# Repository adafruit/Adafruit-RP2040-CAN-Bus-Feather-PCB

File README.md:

## Adafruit RP2040 CAN Bus Feather with MCP2515 CAN Controller - STEMMA QT PCB

<a href="http://www.adafruit.com/products/5724"><br/>
Click here to purchase one from the Adafruit shop</a>

PCB files for the Adafruit RP2040 CAN Bus Feather with MCP2515 CAN Controller - STEMMA QT. 

Format is EagleCAD schematic and board layout
* https://www.adafruit.com/product/5724

### Description

If you'd like to quickly get started with CAN bus interfacing, with no soldering required, our Adafruit RP2040 CAN Bus Feather comes ready-to-rock with a microcontroller, CAN chipset and terminal blocks for instant gratification. The controller used is the MCP26525 (aka a MCP2515 with built-in transciever), an extremely popular and well-supported chipset that has drivers in Arduino and CircuitPython and only requires an SPI port and two pins for chip-select and IRQ. Use it to send and receive messages in either standard or extended format at up to 1 Mbps.

Feather is the development board specification from Adafruit, and like its namesake, it is thin, light, and lets you fly! We designed Feather to be a new standard for portable microcontroller cores. We have other boards in the Feather family, check'em out here.

CAN Bus is a small-scale networking standard, originally designed for cars and, yes, busses, but is now used for many robotics or sensor networks that need better range and addressing than I2C and don't have the pins or computational ability to talk on Ethernet. CAN is 2 wire differential, which means it's good for long distances and noisy environments.

Messages are sent at about 1Mbps rate - you set the frequency for the bus and then all 'joiners' must match it, and have an address before the packet so that each node can listen in to messages just for it. New nodes can be attached easily because they just need to connect to the two data lines anywhere in the shared net. Each CAN device sends messages whenever it wants, and thanks to some clever data encoding, can detect if there's a message collision and retransmit later. 

We've added a few nice extras to this Feather to make it useful in many common CAN scenarios:

* 5V charge-pump voltage generator, so even though you are running 3.3V on a Feather board, it will generate a nice clean 5V as required by the interal transceiver.
* 3.5mm soldered terminal block quick access to the High and Low data lines as well as a ground pin, without any soldering.
* 120-ohm termination resistor on board, you can remove the termination easily by cutting the jumper marked TERM on the top of the board.
* CAN control CS, Reset, Int, standby pins connected internally so you can use any FeatherWing without pin conflicts.

At the Feather's heart is an RP2040 chip, clocked at 133 MHz and at 3.3V logic, the same one used in the Raspberry Pi Pico. This chip has a whopping 8 MB of onboard QSPI FLASH and 264K of RAM!  There's even room left over for a STEMMA QT connector for plug-and-play of I2C devices.

To make it easy to use for portable projects, we added a connector for any of our 3.7V Lithium polymer batteries and built-in battery charging. You don't need a battery, it will run just fine straight from the USB Type C connector. But, if you do have a battery, you can take it on the go, then plug in the USB to recharge. The Feather will automatically switch over to USB power when it's available.

Here're some handy specs! You get:

* Measures 2.0" x 0.9" x 0.28" (50.8mm x 22.8mm x 7mm) without headers soldered in
* Light as a (large?) feather - 6.3 grams
* RP2040 32-bit Cortex M0+ dual core running at ~133 MHz @ 3.3V logic and power
* 264 KB RAM
* 8 MB SPI FLASH chip for storing files, images and CircuitPython/MicroPython code storage. No EEPROM
* Tons of GPIO! 21 x GPIO pins with following capabilities:
	* Four 12-bit ADCs (one more than Pico)
	* Two I2C, Two SPI, and two UART peripherals, we label one for the 'main' interface in standard Feather locations
	* 16 x PWM outputs - for servos, LEDs, etc
* Built-in 200mA+ lipoly charger with charging status indicator LED
* Pin #13 red LED for general purpose blinking
* RGB NeoPixel for full-color indication.
* On-board STEMMA QT connector that lets you quickly connect any Qwiic, STEMMA QT or Grove I2C devices with no soldering!
* Both Reset button and Bootloader select button for quick restarts (no unplugging-replugging to relaunch code)
* USB Type C connector lets you access built-in ROM USB bootloader and serial port debugging
* 3.3V regulator with 500mA peak current output and power enable pin
* 4 mounting holes
* 12 MHz crystal for perfect timing.
* Support circuitry for CAN Bus using SPI interface

Comes assembled and tested, with some header. You'll need a soldering iron to attach the header for installing onto your Feather. Stacking headers will let you put another FeatherWing on top.

### License

Adafruit invests time and resources providing this open source design, please support Adafruit and open-source hardware by purchasing products from [Adafruit](https://www.adafruit.com)!

Designed by Limor Fried/Ladyada for Adafruit Industries.

Creative Commons Attribution/Share-Alike, all text above must be included in any redistribution. 
See license.txt for additional details.

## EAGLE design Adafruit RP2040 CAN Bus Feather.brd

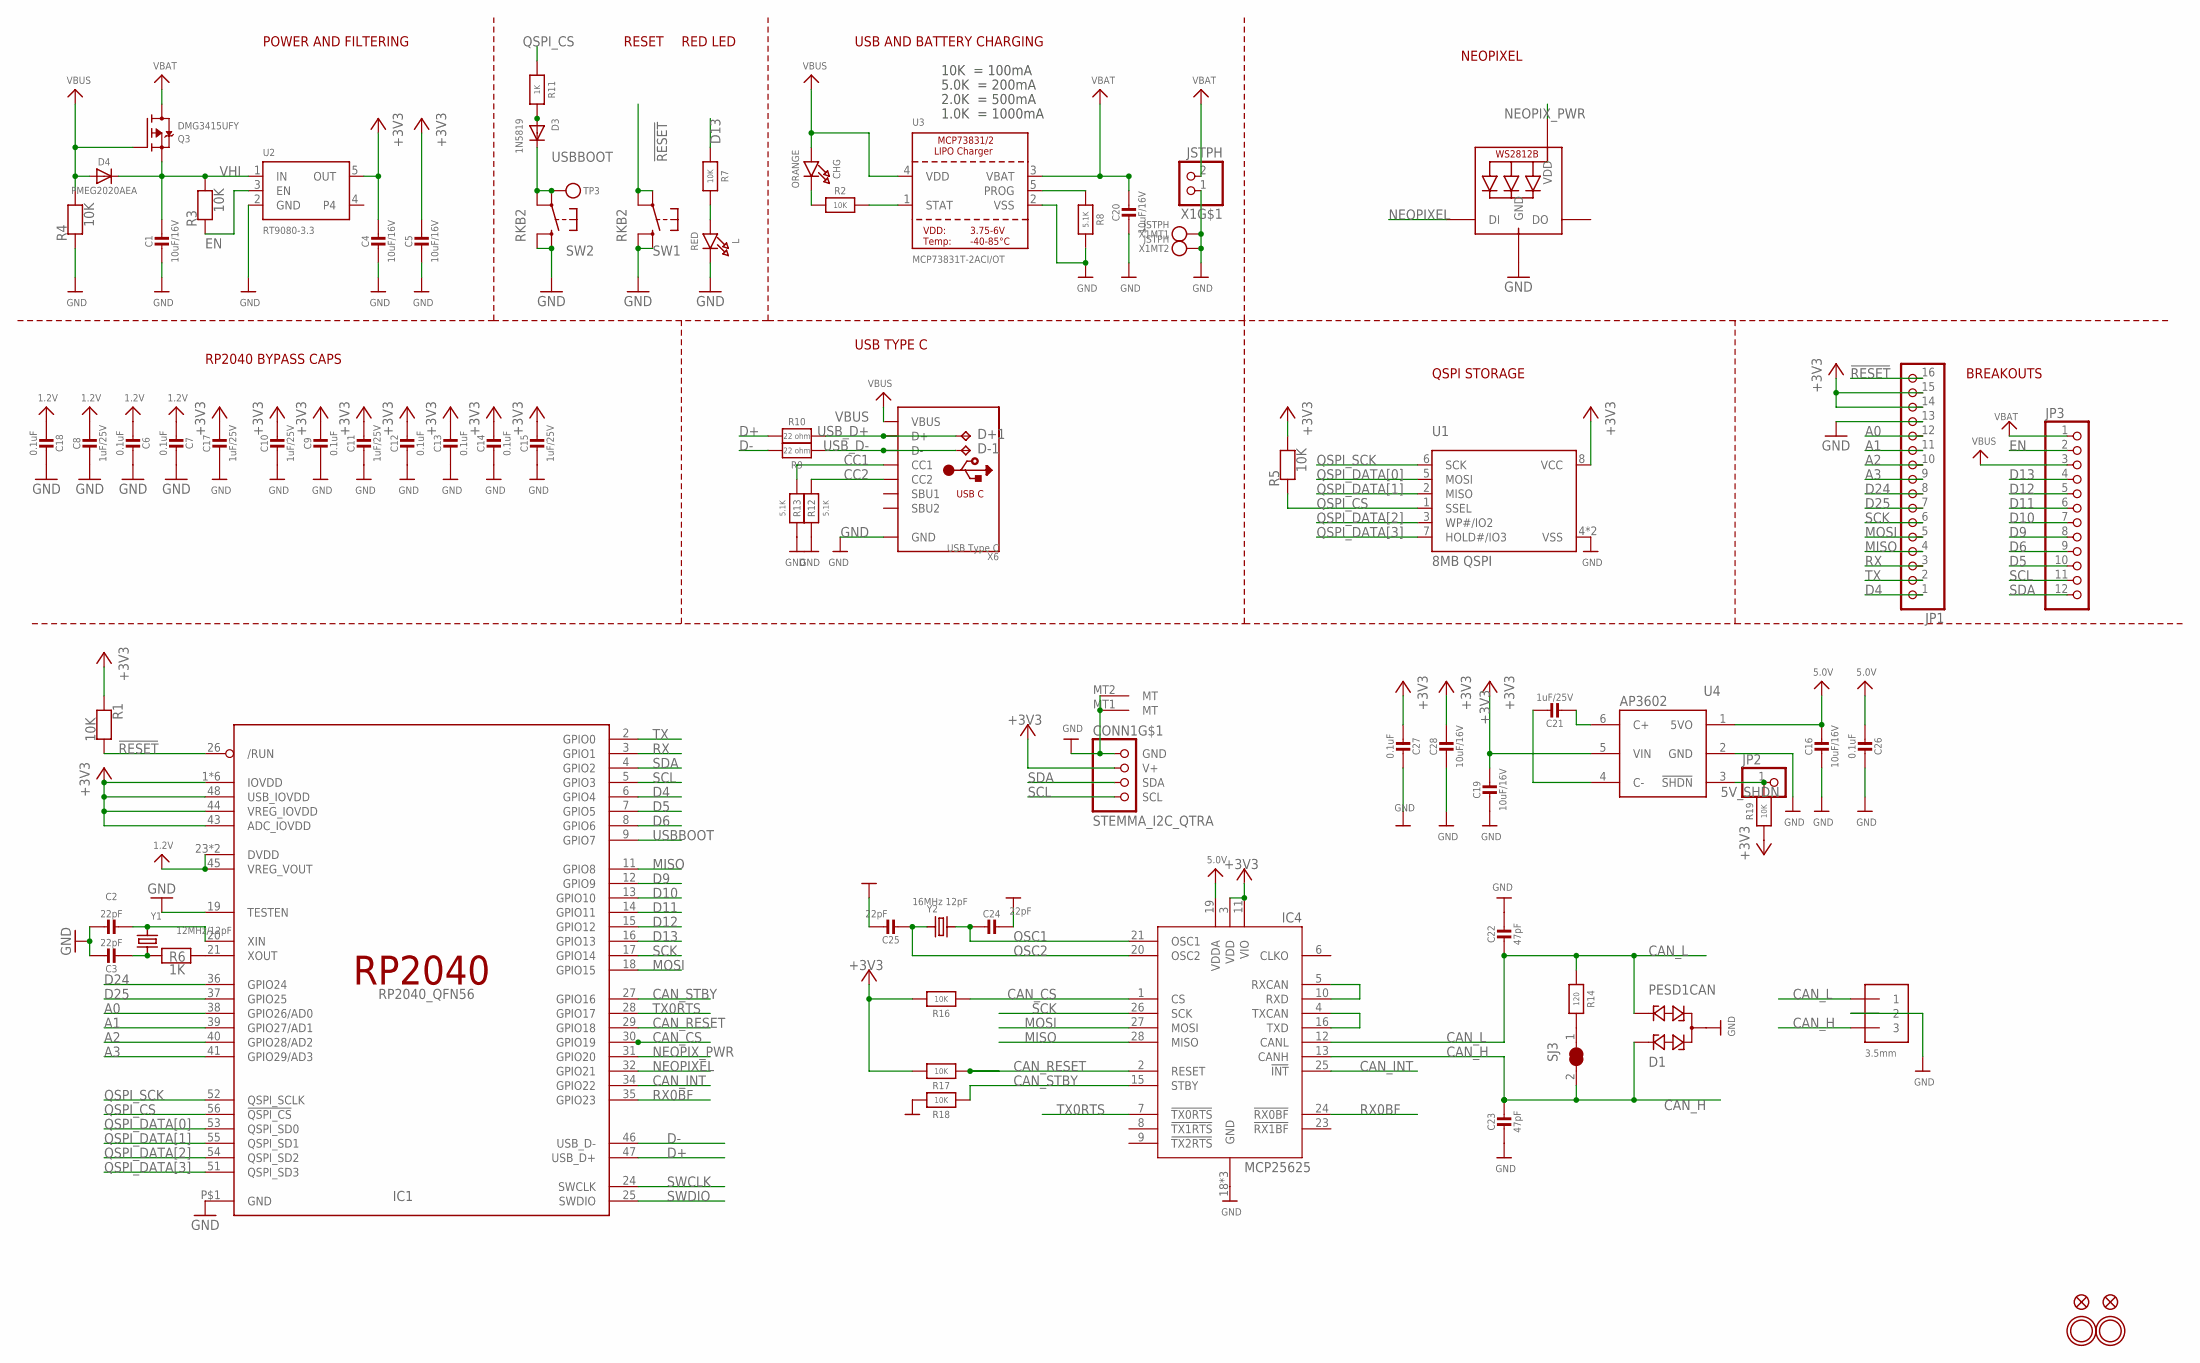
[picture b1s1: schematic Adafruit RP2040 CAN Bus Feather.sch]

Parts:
C1, C4, C5, C16, C19, C20, C28: 10uF/16V; 0805-NO
C2, C3, C24, C25: 22pF; _0402NO
C6, C7, C9, C12, C13, C14, C18, C26, C27: 0.1uF; _0402NO
C8, C10, C11, C15, C17, C21: 1uF/25V; _0402NO
C22, C23: 47pF; _0402NO
CHG: ORANGE; CHIPLED_0603_NOOUTLINE
CONN1: STEMMA_I2C_QTRA; JST_SH4_RA
D1: PESD1CAN; SOT23
D3: 1N5819; SOD-323_MINI
D4: PMEG2020AEA; SOD-323F
D+1: TPB1,27; B1,27
D-1: TPB1,27; B1,27
IC1: RP2040_QFN56; QFN56_7MM_REDUCEDEPAD
IC4: MCP25625; QFN28-ML_6X6MM
JP1: HEADER-1X16ROUND; 1X16_ROUND
JP2: HEADER-1X12MM; 1X01_2MM
JP3: HEADER-1X12; 1X12_ROUND
L: RED; CHIPLED_0603_NOOUTLINE
LED1: WS2812B_SK6805_1515; SK6805_1515
NEOPIX1: 3.5mm; TERMBLOCK_1X3-3.5MM
Q3: DMG3415UFY; DFN2015-3
R1, R2, R3, R4, R5, R7, R16, R17, R18, R19: 10K; _0402NO
R6, R11: 1K; _0402NO
R8, R12, R13: 5.1K; _0402NO
R9, R10: 22 ohm; _0402NO
R14: 120; _0402NO
SJ3: SOLDERJUMPER_CLOSED; SOLDERJUMPER_CLOSEDWIRE
SW1, SW2: RKB2; BTN_RKB2_4.6X2.8
TP3: TESTPOINTROUND1.5MMNO; TESTPOINT_ROUND_1.5MM_NO
U1: 8MB QSPI; USON8_4X4
U2: RT9080-3.3; SOT23-5; JLC_ROTATION 0
U3: MCP73831T-2ACI/OT; SOT23-5
U4: AP3602; SOT23-6
U$31, U$32: MOUNTINGHOLE2.5; MOUNTINGHOLE_2.5_PLATED
U$34, U$35: FIDUCIAL_1MM
X1: JSTPH; JSTPH2_BATT
X6: USB Type C; USB_C_CUSB31-CFM2AX-01-X
Y1: 12MHz/12pF; CRYSTAL_2.5X2
Y2: 16MHz 12pF; CRYSTAL_2.5X2

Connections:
1.2V: C6.2, C7.2, C8.1, C18.2, IC1.23 (DVDD), IC1.45 (VREG_VOUT), IC1.50 (DVDD)
5.0V: C16.1, C26.2, IC4.19 (VDDA), U4.1 (5VO)
5V_SHDN: JP2.1, R19.2, U4.3 (!SHDN)
!RESET: IC1.26 (/RUN), JP1.16, R1.2, SW1.A, SW1.A' (P1)
+3V3: C4.1, C5.1, C9.1, C10.1, C11.1, C12.1, C13.1, C14.1, C15.1, C17.1, C19.1, C27.2, C28.1, CONN1.2 (V+), IC1.1 (IOVDD), IC1.10 (IOVDD), IC1.22 (IOVDD), IC1.33 (IOVDD), IC1.42 (IOVDD), IC1.43 (ADC_IOVDD), IC1.44 (VREG_IOVDD), IC1.48 (USB_IOVDD), IC1.49 (IOVDD), IC4.3 (VDD), IC4.11 (VIO), JP1.14, JP1.15, R1.1, R5.2, R16.2, R17.2, R19.1, U1.8 (VCC), U2.5 (OUT), U4.5 (VIN)
A0: IC1.38 (GPIO26/AD0), JP1.12
A1: IC1.39 (GPIO27/AD1), JP1.11
A2: IC1.40 (GPIO28/AD2), JP1.10
A3: IC1.41 (GPIO29/AD3), JP1.9
CAN_CS: IC1.30 (GPIO19), IC4.1 (CS), R16.1
CAN_H: C23.1, D1.1, IC4.13 (CANH), NEOPIX1.3, SJ3.2
CAN_INT: IC1.34 (GPIO22), IC4.25 (!INT)
CAN_L: C22.2, D1.2, IC4.12 (CANL), NEOPIX1.1, R14.1
CAN_RESET: IC1.29 (GPIO18), IC4.2 (RESET), R17.1
CAN_STBY: IC1.27 (GPIO16), IC4.15 (STBY), R18.1
CC1: R13.2, X6.A5 (CC1)
CC2: R12.2, X6.B5 (CC2)
D4: IC1.6 (GPIO4), JP1.1
D5: IC1.7 (GPIO5), JP3.10
D6: IC1.8 (GPIO6), JP3.9
D9: IC1.12 (GPIO9), JP3.8
D10: IC1.13 (GPIO10), JP3.7
D11: IC1.14 (GPIO11), JP3.6
D12: IC1.15 (GPIO12), JP3.5
D13: IC1.16 (GPIO13), JP3.4, R7.1
D24: IC1.36 (GPIO24), JP1.8
D25: IC1.37 (GPIO25), JP1.7
D+: IC1.47 (USB_D+), R10.2
D-: IC1.46 (USB_D-), R9.2
EN: JP3.2, R3.1, U2.3 (EN)
GND: C1.2, C2.1, C3.1, C4.2, C5.2, C6.1, C7.1, C8.2, C9.2, C10.2, C11.2, C12.2, C13.2, C14.2, C15.2, C16.2, C17.2, C18.1, C19.2, C20.2, C22.1, C23.2, C24.1, C25.1, C26.1, C27.1, C28.2, CONN1.1 (GND), CONN1.MT1 (MT), CONN1.MT2 (MT), D1.3, IC1.19 (TESTEN), IC1.P$1 (GND), IC4.18 (GND), IC4.22 (GND), IC4.EXP (GND), JP1.13, L.C, LED1.4 (GND), NEOPIX1.2, R4.1, R8.2, R12.1, R13.1, R18.2, SW1.B (S), SW1.B' (S1), SW2.B (S), SW2.B' (S1), U1.4 (VSS), U1.PAD (VSS), U2.2 (GND), U3.2 (VSS), U4.2 (GND), X1.1, X1.NC1, X1.NC2, X6.A1B12 (GND), X6.B1A12 (GND)
MISO: IC1.11 (GPIO8), IC4.28 (MISO), JP1.4
MOSI: IC1.18 (GPIO15), IC4.27 (MOSI), JP1.5
unnamed: CHG.C, R2.1
unnamed: L.A, R7.2
unnamed: R2.2, U3.1 (STAT)
unnamed: R8.1, U3.5 (PROG)
unnamed: C2.2, IC1.20 (XIN), Y1.3 (2)
unnamed: C3.2, R6.1, Y1.1
unnamed: IC1.21 (XOUT), R6.2
unnamed: C21.1, U4.4 (C-)
unnamed: C21.2, U4.6 (C+)
unnamed: R14.2, SJ3.1
unnamed: IC4.5 (RXCAN), IC4.10 (RXD)
unnamed: IC4.4 (TXCAN), IC4.16 (TXD)
unnamed: D3.A, R11.2
NEOPIXEL: IC1.32 (GPIO21), LED1.1 (DI)
NEOPIX_PWR: IC1.31 (GPIO20), LED1.2 (VDD)
OSC1: C24.2, IC4.21 (OSC1), Y2.3 (2)
OSC2: C25.2, IC4.20 (OSC2), Y2.1
QSPI_CS: IC1.56 (!QSPI_CS), R5.1, R11.1, U1.1 (SSEL)
QSPI_DATA[0]: IC1.53 (QSPI_SD0), U1.5 (MOSI)
QSPI_DATA[1]: IC1.55 (QSPI_SD1), U1.2 (MISO)
QSPI_DATA[2]: IC1.54 (QSPI_SD2), U1.3 (WP#/IO2)
QSPI_DATA[3]: IC1.51 (QSPI_SD3), U1.7 (HOLD#/IO3)
QSPI_SCK: IC1.52 (QSPI_SCLK), U1.6 (SCK)
RX: IC1.3 (GPIO1), JP1.3
RX0BF: IC1.35 (GPIO23), IC4.24 (!RX0BF)
SCK: IC1.17 (GPIO14), IC4.26 (SCK), JP1.6
SCL: CONN1.4 (SCL), IC1.5 (GPIO3), JP3.11
SDA: CONN1.3 (SDA), IC1.4 (GPIO2), JP3.12
SWCLK: IC1.24 (SWCLK)
SWDIO: IC1.25 (SWDIO)
TX: IC1.2 (GPIO0), JP1.2
TX0RTS: IC1.28 (GPIO17), IC4.7 (!TX0RTS)
USBBOOT: D3.C, IC1.9 (GPIO7), SW2.A, SW2.A' (P1), TP3.P$1
USB_D+: D+1.TP, R10.1, X6.A6 (D+), X6.B6 (D+)
USB_D-: D-1.TP, R9.1, X6.A7 (D-), X6.B7 (D-)
VBAT: C20.1, JP3.1, Q3.3 (D), U3.3 (VBAT), X1.2
VBUS: CHG.A, D4.A, JP3.3, Q3.1 (G), R4.2, U3.4 (VDD), X6.A4B9 (VBUS), X6.B4A9 (VBUS)
VHI: C1.1, D4.C, Q3.2 (S), R3.2, U2.1 (IN)

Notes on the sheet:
POWER AND FILTERING
RESET
10K = 100mA
5.0K = 200mA
2.0K = 500mA
1.0K = 1000mA
USB AND BATTERY CHARGING
BREAKOUTS
RED LED
RP2040 BYPASS CAPS
USB TYPE C
QSPI STORAGE
NEOPIXEL

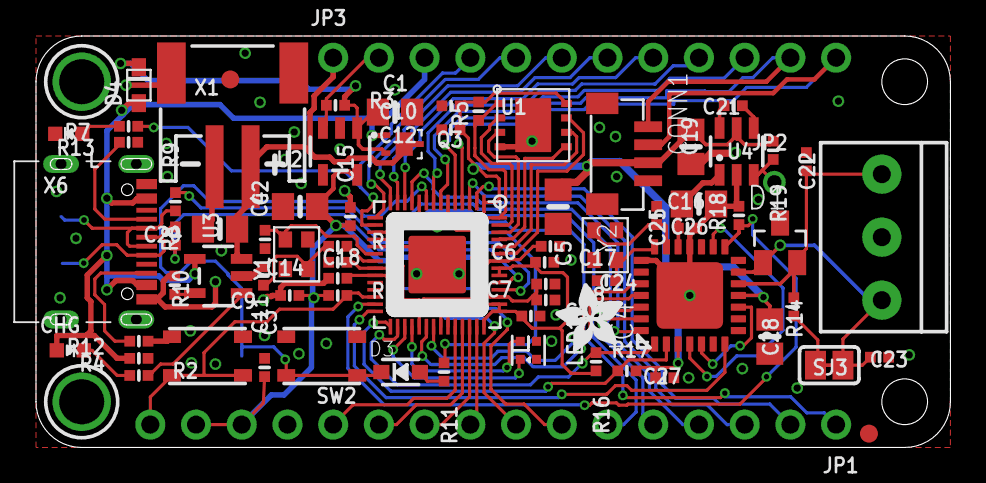
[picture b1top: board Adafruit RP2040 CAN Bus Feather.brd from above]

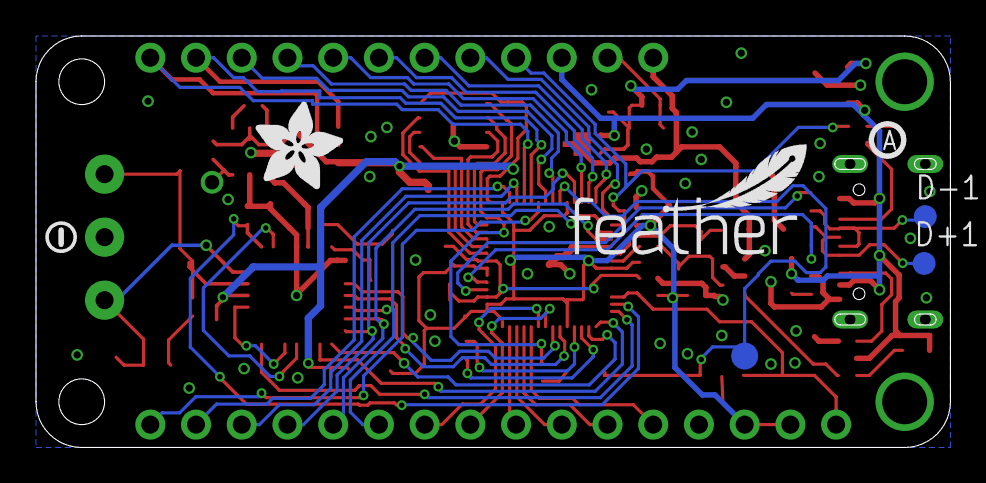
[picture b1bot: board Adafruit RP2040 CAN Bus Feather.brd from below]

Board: 2 copper layers, 50.8 x 22.9 mm, 153 parts (40 on the bottom side), 69 nets.

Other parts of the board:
PLABEL0: PLABEL0
PLABEL1: PLABEL1
PLABEL2: PLABEL2
PLABEL3: PLABEL3
PLABEL4: PLABEL4
PLABEL5: PLABEL5
PLABEL6: PLABEL6
PLABEL7: PLABEL7
PLABEL8: PLABEL8
PLABEL9: PLABEL9
PLABEL10: PLABEL10
PLABEL11: PLABEL11
PLABEL12: PLABEL12
PLABEL13: PLABEL13
PLABEL14: PLABEL14
PLABEL15: PLABEL15
PLABEL16: PLABEL16
PLABEL17: PLABEL17
PLABEL18: PLABEL18
PLABEL19: PLABEL19
PLABEL20: PLABEL20
PLABEL21: PLABEL21
PLABEL22: PLABEL22
PLABEL23: PLABEL23
PLABEL24: PLABEL24
PLABEL25: PLABEL25
PLABEL26: PLABEL26
PLABEL27: PLABEL27
PLABEL28: PLABEL28
PLABEL29: PLABEL29
PLABEL30: PLABEL30
PLABEL31: PLABEL31
PLABEL32: PLABEL32
PLABEL33: PLABEL33
PLABEL34: PLABEL34
PLABEL35: PLABEL35
PLABEL36: PLABEL36
PLABEL37: PLABEL37
PLABEL38: PLABEL38
PLABEL39: PLABEL39
PLABEL40: PLABEL40
PLABEL41: PLABEL41
PLABEL42: PLABEL42
PLABEL43: PLABEL43
PLABEL44: PLABEL44
PLABEL45: PLABEL45
PLABEL46: PLABEL46
PLABEL47: PLABEL47
PLABEL48: PLABEL48
PLABEL49: PLABEL49
PLABEL50: PLABEL50
PLABEL51: PLABEL51
PLABEL52: PLABEL52
PLABEL53: PLABEL53
PLABEL54: PLABEL54
PLABEL55: PLABEL55
PLABEL56: PLABEL56
PLABEL57: PLABEL57
PLABEL58: PLABEL58
PLABEL59: PLABEL59
PLABEL60: PLABEL60
PLABEL61: PLABEL61
PLABEL62: PLABEL62
PLABEL63: PLABEL63
PLABEL64: PLABEL64
PLABEL65: PLABEL65
PLABEL66: PLABEL66
PLABEL67: PLABEL67
PLABEL68: PLABEL68
PLABEL69: PLABEL69
U$13: PCBFEAT-REV-040
U$42: ADAFRUIT_3.5MM
U$53: SYMBOL_MINUS
U$54: ADAFRUIT_5MM
U$60: FEATHERLOGO_SMALL

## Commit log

2023-05-03 adding cookiecutter output
2023-05-03 typo
2023-05-03 adding factory reset folder
2023-05-10 adding prettypins
2023-05-10 adding factory reset

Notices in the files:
parts and their libraries:
microbuilder: This work is placed in the public domain, and may be freely used for commercial and non-commercial work with the following conditions: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
